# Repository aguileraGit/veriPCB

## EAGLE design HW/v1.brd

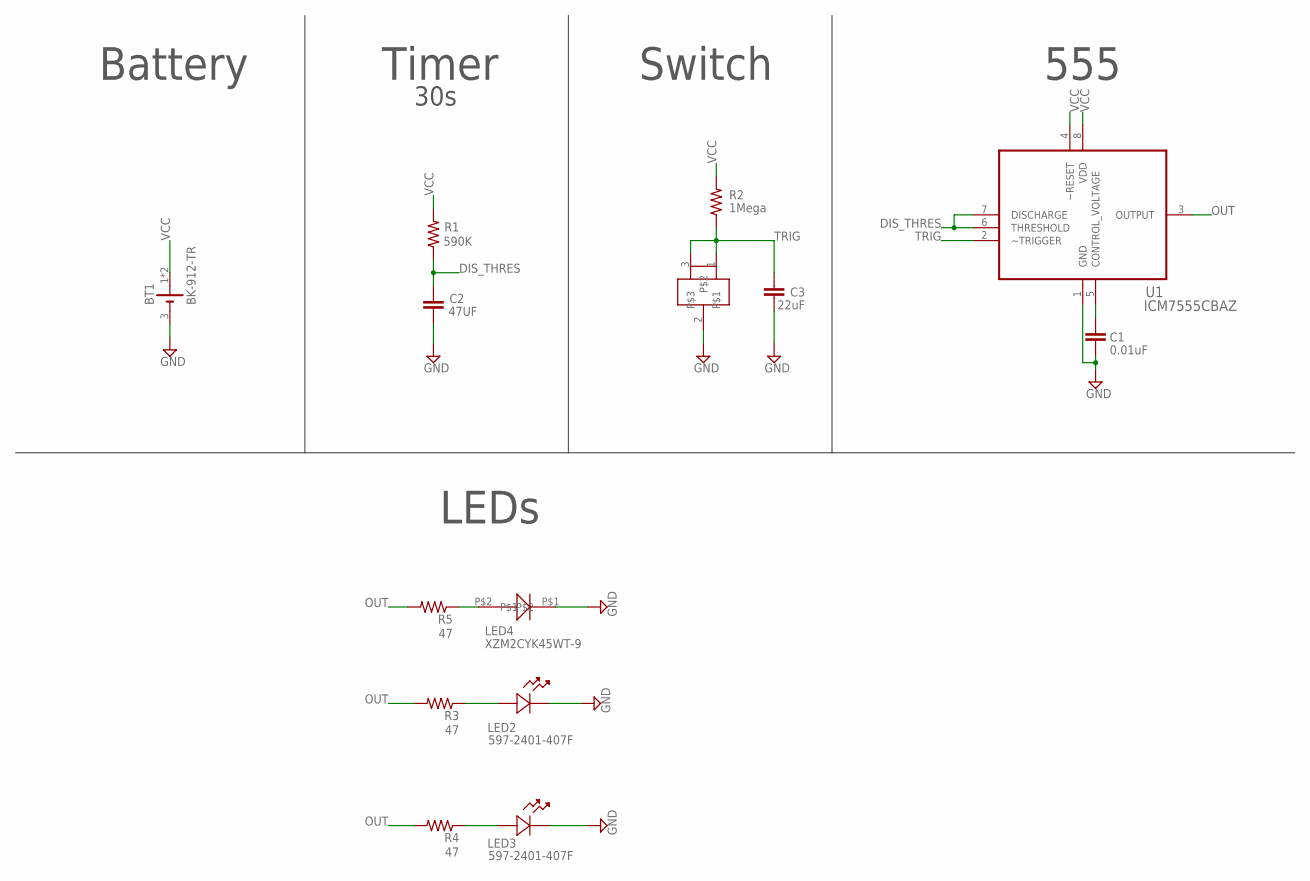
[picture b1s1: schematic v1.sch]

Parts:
BT1: BK-912-TR; MPD_BK-912-TR
C1: 0.01uF; C0603
C2: 47UF; C0603
C3: 22uF; C0603
LED2, LED3: 597-2401-407F; LED_597-2401-407F
LED4: XZM2CYK45WT-9; XZM2CYK45WT
R1: 590K; R0603
R2: 1Mega; R0603
R3, R4, R5: 47; R0603
SW1: TM1000Q; SIP750W46P254L1400H1010Q3
U1: ICM7555CBAZ; SOIC127P600X175-8N

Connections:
DIS_THRES: C2.2, R1.1, U1.6 (THRESHOLD), U1.7 (DISCHARGE)
GND: BT1.3 (-), C1.1, C2.1, C3.1, LED2.1, LED3.1, LED4.P$1, SW1.2, U1.1 (GND)
unnamed: C1.2, U1.5 (CONTROL_VOLTAGE)
unnamed: LED2.2, R3.1
unnamed: LED3.2, R4.1
unnamed: LED4.P$2, R5.1
OUT: R3.2, R4.2, R5.2, U1.3 (OUTPUT)
TRIG: C3.2, R2.1, SW1.1, SW1.3, U1.2 (~TRIGGER)
VCC: BT1.1 (+), BT1.2 (+), R1.2, R2.2, U1.4 (~RESET), U1.8 (VDD)

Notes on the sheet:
Battery
Timer
Switch
555
LEDs
30s

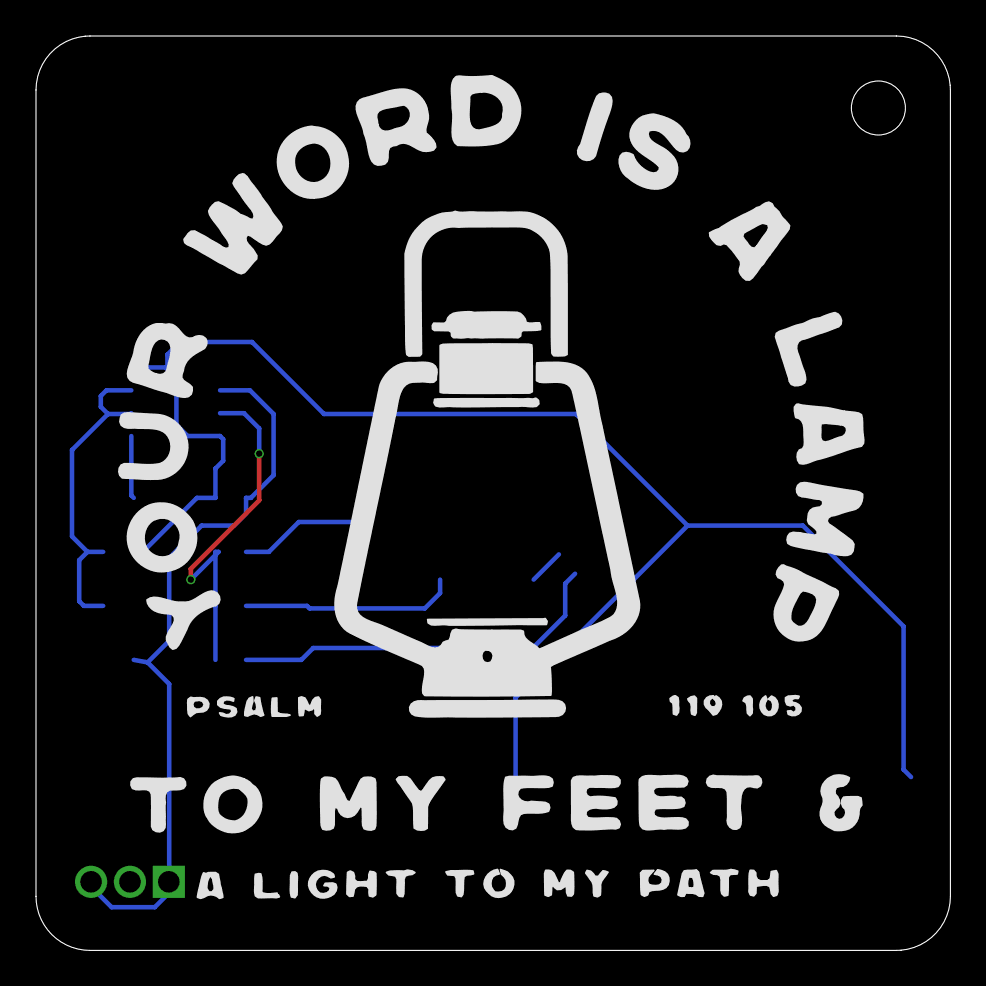
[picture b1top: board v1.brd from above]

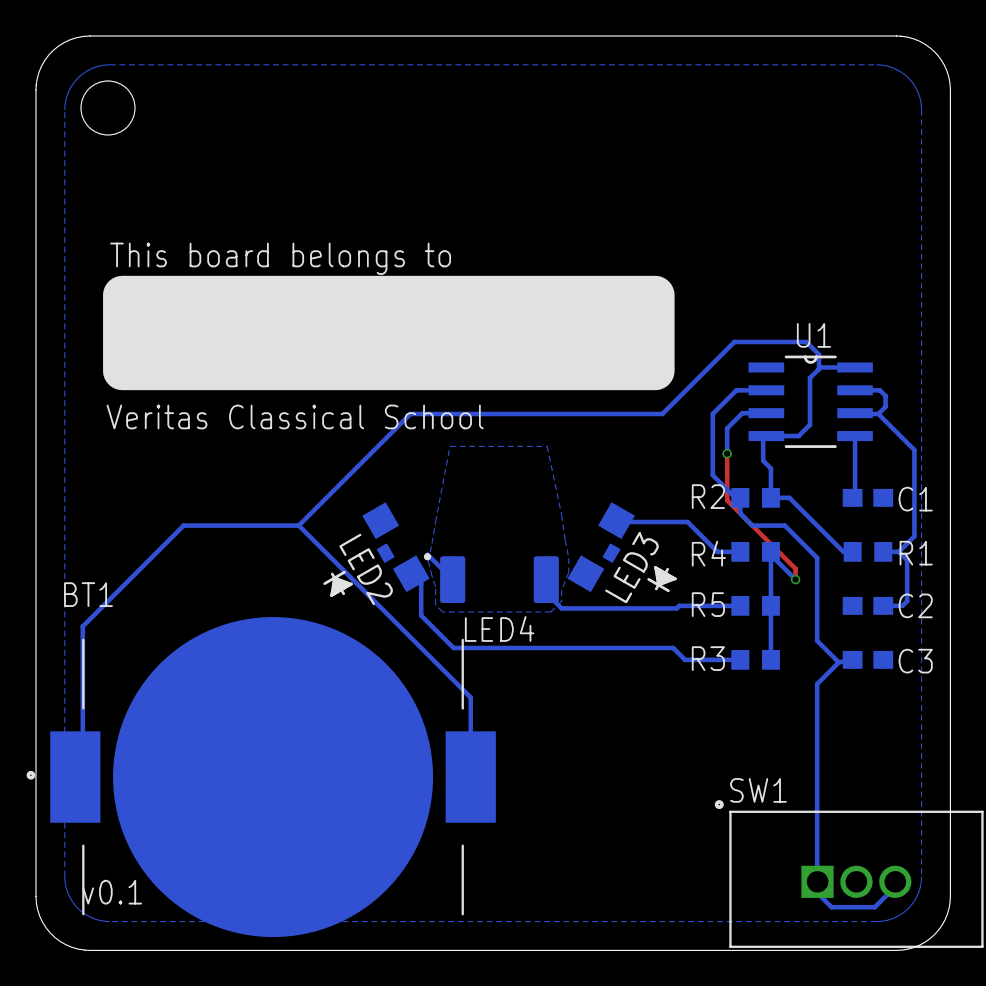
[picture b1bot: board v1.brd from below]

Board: 2 copper layers, 50.8 x 50.8 mm, 14 parts (14 on the bottom side), 9 nets.

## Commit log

2023-07-31 Adding PCB files
2023-07-31 Added ignore
2023-07-31 Update gitignore
2023-07-31 Remove .DS_Store from everywhere
